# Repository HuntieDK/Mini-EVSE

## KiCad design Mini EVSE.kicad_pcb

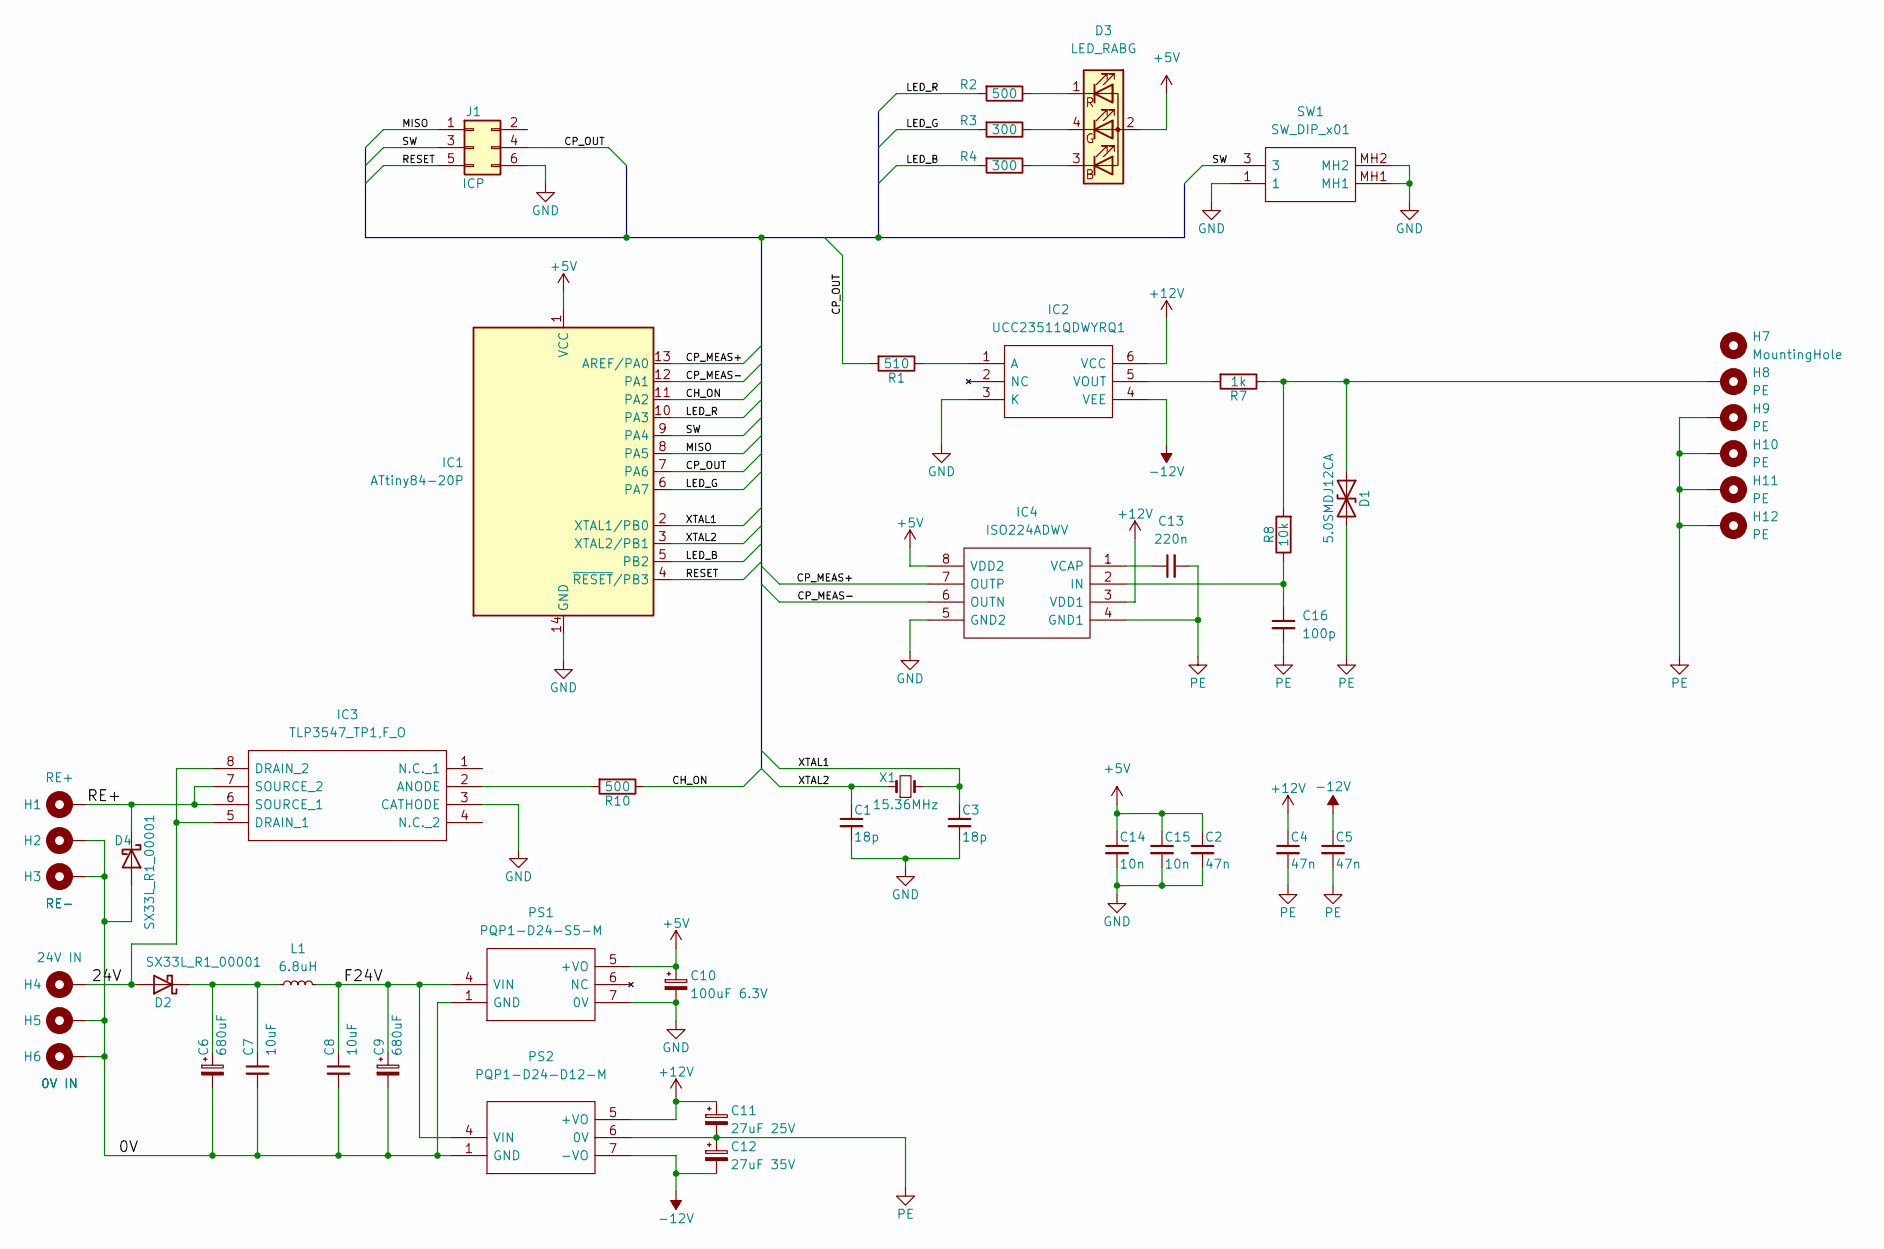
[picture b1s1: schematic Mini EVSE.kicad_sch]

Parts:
C1, C3: 18p; C_1206_3216Metric_Pad1.33x1.80mm_HandSolder
C2, C4, C5: 47n; C_1206_3216Metric_Pad1.33x1.80mm_HandSolder
C6, C9: 680uF; CP_Elec_10x10.5
C7, C8: 10uF; C_1206_3216Metric_Pad1.33x1.80mm_HandSolder
C10: 100uF 6.3V; CP_Elec_6.3x5.9
C11: 27uF 25V; CP_Elec_5x5.8
C12: 27uF 35V; CP_Elec_5x5.8
C13: 220n; C_1206_3216Metric_Pad1.33x1.80mm_HandSolder
C14, C15: 10n; C_1206_3216Metric_Pad1.33x1.80mm_HandSolder
C16: 100p; C_1206_3216Metric_Pad1.33x1.80mm_HandSolder
D1: 5.0SMDJ12CA; D_SMC
D2, D4: SX33L_R1_00001; D_SMA_Handsoldering
D3: LED_RABG; 5504013F
H1: RE+; TestPoint_Loop_D2.60mm_Drill1.4mm_Beaded
H2, H3: RE-; TestPoint_Loop_D2.60mm_Drill1.4mm_Beaded
H4: 24V IN; TestPoint_Loop_D2.60mm_Drill1.4mm_Beaded
H5, H6: 0V IN; TestPoint_Loop_D2.60mm_Drill1.4mm_Beaded
H7: MountingHole; MountingHole_2.1mm
H8, H9, H10, H11, H12: PE; TestPoint_Loop_D2.60mm_Drill1.4mm_Beaded
IC1: ATtiny84-20P; SOIC-14_3.9x8.7mm_P1.27mm
IC2: UCC23511QDWYRQ1; SOIC127P1150X355-6N; Mouser Part Number 595-UCC23511QDWYRQ1
IC3: TLP3547_TP1,F_O; SOP254P1000X425-8N; Manufacturer_Part_Number TLP3547(TP1,F(O
IC4: ISO224ADWV; SOIC127P1150X280-8N; Manufacturer_Part_Number ISO224ADWV; Mouser Part Number 595-ISO224ADWV
J1: ICP; PinHeader_2x03_P2.54mm_Vertical
L1: 6.8uH; L_1210_3225Metric_Pad1.42x2.65mm_HandSolder
PS1: PQP1-D24-S5-M; PQP1D24S5M; Manufacturer_Part_Number PQP1-D24-S5-M; Mouser Part Number 490-PQP1-D24-S5-M
PS2: PQP1-D24-D12-M; PQP1D24S5M; Manufacturer_Part_Number PQP1-D24-S5-M; Mouser Part Number 490-PQP1-D24-S5-M
R1: 510; R_1206_3216Metric_Pad1.30x1.75mm_HandSolder
R2, R10: 500; R_1206_3216Metric_Pad1.30x1.75mm_HandSolder
R3, R4: 300; R_1206_3216Metric_Pad1.30x1.75mm_HandSolder
R7: 1k; R_1206_3216Metric_Pad1.30x1.75mm_HandSolder
R8: 10k; R_1206_3216Metric_Pad1.30x1.75mm_HandSolder
SW1: SW_DIP_x01; TPA11CGRA004; Mouser Part Number 506-TPA11CGRA004
X1: 15.36MHz; Crystal_HC49-U_Vertical

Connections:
+5V: C2.1, C10.1, C14.1, C15.1, D3.2 (A), IC1.1 (VCC), IC4.8 (VDD2), PS1.5 (+VO)
+12V: C4.1, C11.1, IC2.6 (VCC), IC4.3 (VDD1), PS2.5 (+VO)
-12V: C5.1, C12.2, IC2.4 (VEE), PS2.7 (-VO)
/0V: C6.2, C7.2, C8.2, C9.2, D4.2 (A), H2.1, H3.1, H5.1, H6.1, PS1.1 (GND), PS2.1 (GND)
/24V: D2.2 (A), H4.1, IC3.5 (DRAIN_1), IC3.8 (DRAIN_2)
/CH_ON: IC1.11 (PA2), R10.1
/CP_MEAS+: IC1.13 (AREF/PA0), IC4.7 (OUTP)
/CP_MEAS-: IC1.12 (PA1), IC4.6 (OUTN)
/CP_OUT: IC1.7 (PA6), J1.4, R1.2
/F24V: C8.1, C9.1, L1.2, PS1.4 (VIN), PS2.4 (VIN)
/LED_B: IC1.5 (PB2), R4.2
/LED_G: IC1.6 (PA7), R3.2
/LED_R: IC1.10 (PA3), R2.2
/MISO: IC1.8 (PA5), J1.1
/RE+: D4.1 (K), H1.1, IC3.6 (SOURCE_1), IC3.7 (SOURCE_2)
/RESET: IC1.4 (~RESET/PB3), J1.5
/SW: IC1.9 (PA4), J1.3, SW1.3
/XTAL1: C3.1, IC1.2 (XTAL1/PB0), X1.2
/XTAL2: C1.1, IC1.3 (XTAL2/PB1), X1.1
GND: C1.2, C2.2, C3.2, C10.2, C14.2, C15.2, IC1.14 (GND), IC2.3 (K), IC3.3 (CATHODE), IC4.5 (GND2), J1.6, PS1.7 (0V), SW1.1, SW1.MH1, SW1.MH2
unnamed: C6.1, C7.1, D2.1 (K), L1.1
unnamed: C13.1, IC4.1 (VCAP)
unnamed: D1.1 (A1), H8.1, R7.1, R8.2
unnamed: D3.1 (RK), R2.1
unnamed: D3.3 (BK), R4.1
unnamed: D3.4 (GK), R3.1
unnamed: IC2.1 (A), R1.1
unnamed: IC2.5 (VOUT), R7.2
unnamed: IC3.2 (ANODE), R10.2
unnamed: C16.1, IC4.2 (IN), R8.1
PE: C4.2, C5.2, C11.2, C12.1, C13.2, C16.2, D1.2 (A2), H9.1, H10.1, H11.1, H12.1, IC4.4 (GND1), PS2.6 (0V)

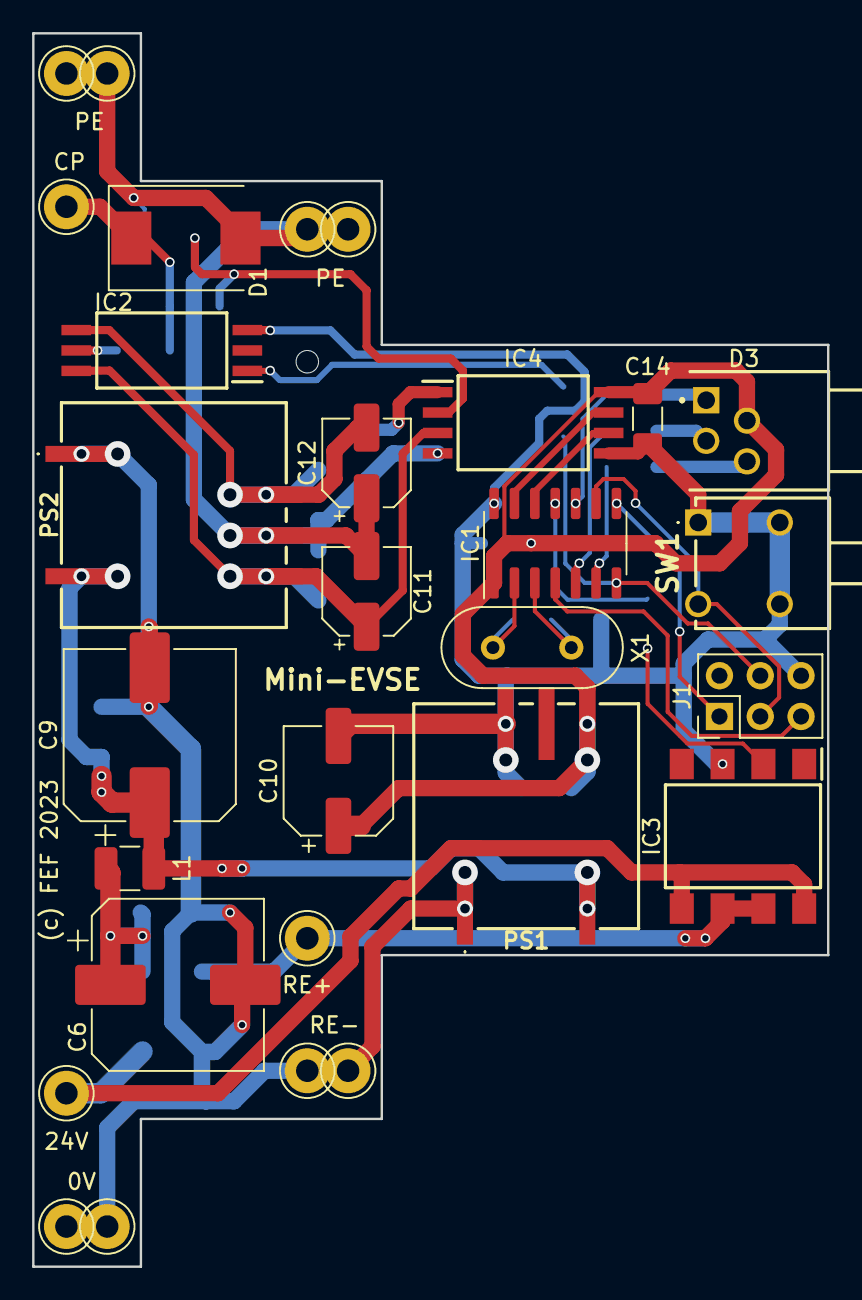
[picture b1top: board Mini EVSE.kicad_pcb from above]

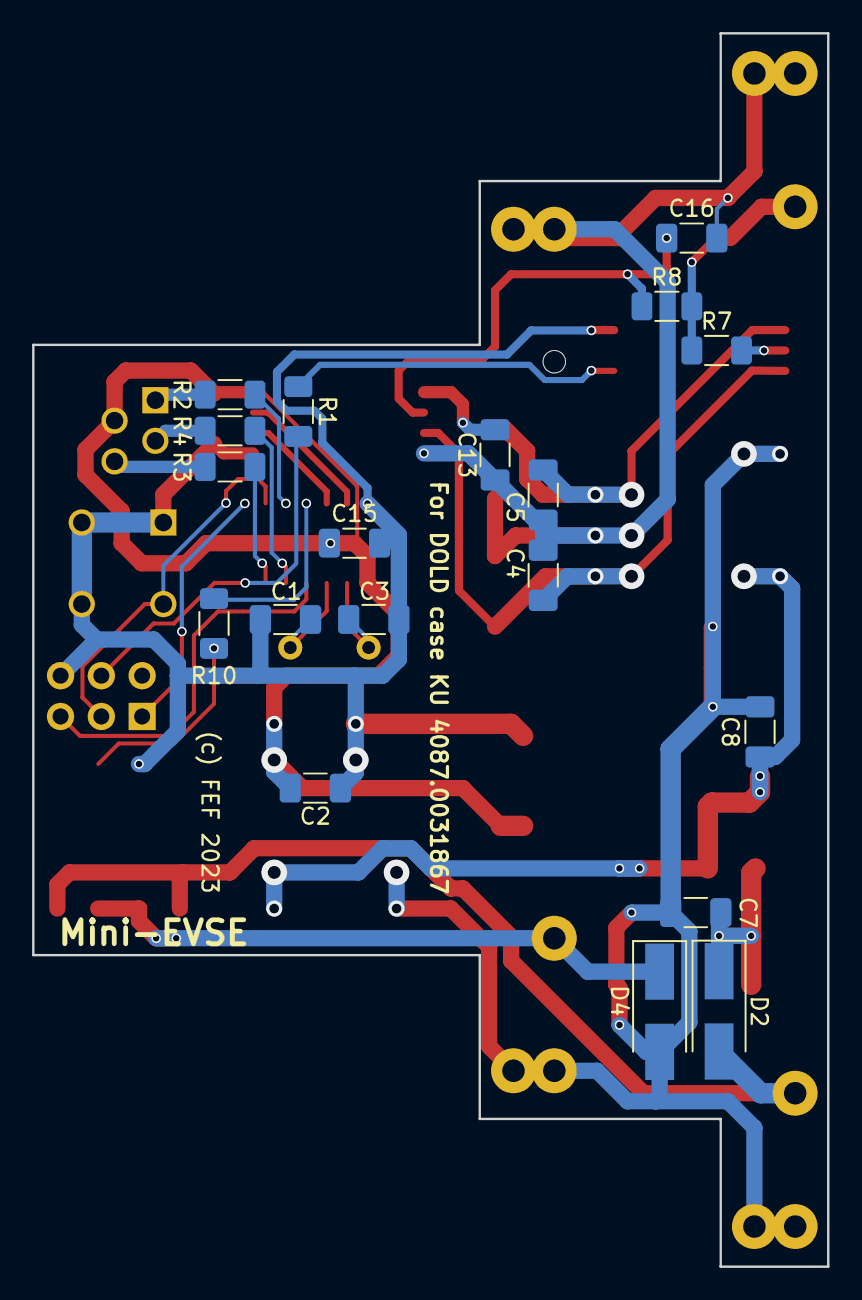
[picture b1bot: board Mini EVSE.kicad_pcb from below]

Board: 2 copper layers, 49.5 x 76.8 mm, 49 parts (19 on the bottom side), 31 nets.

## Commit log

2017-08-26 Added initial Mini EVSE schematics (incomplete)
2017-08-30 Added PSU
2017-08-30 Project path setup
2017-08-30 Added footprints
2017-08-30 Added SSR relay for main contactor
2017-09-01 Small schematics changes. Added PCB layout
2017-09-01 Added license
2017-09-06 Redone PCB design, now 60x70mm. A few schematics changes to make PCB routing easier.
2017-09-09 Changed some pad sixes, component values
2017-09-12 Changed DC/DC converter to TMR1-0522
2017-09-16 Moved switch from reset pin as we need reset to be active for simple ISP.
2018-09-08 Started working on three-phase setup
2018-09-08 Working on 3-phase version - asssigned all MCU pins
2019-05-11 Various improvements
2019-05-11 Updated library submodule
2019-05-15 Added extra components in library
2019-05-27 Adding neutral contact failure detection and ground detection
2019-05-29 Parts update
2019-05-29 Added Phoenix footprints
2019-05-29 Add some footprints
2019-05-30 - Switching to SMD - Starting PCB layout
2023-01-18 Updated to latest libraries
2023-01-18 Update to Kicad 5
2023-04-05 Working on upgrading to KiCAD 6
2023-04-05 Removed need for rescue library
2023-04-05 Updated ATTINY84 version to KiCAD 6
2023-04-12 Changed supply to 24VDC with isolation
2023-04-30 Added PCB layout for DIN rail version
2023-05-01 Fixes to PCB layout - first prototype
2023-05-07 Changed to correct switch connector
2023-05-07 Project update
2023-05-07 Updated solid state relay
2023-05-29 Working on better EMC immunity
2023-06-09 Better EMC protection
2023-06-10 More decoupling, layout adjustments
2023-06-10 Added possible input decoupling cap
2023-06-10 Improved saftety distances
2023-06-10 Final touch
2023-06-10 A bit more safety distance
